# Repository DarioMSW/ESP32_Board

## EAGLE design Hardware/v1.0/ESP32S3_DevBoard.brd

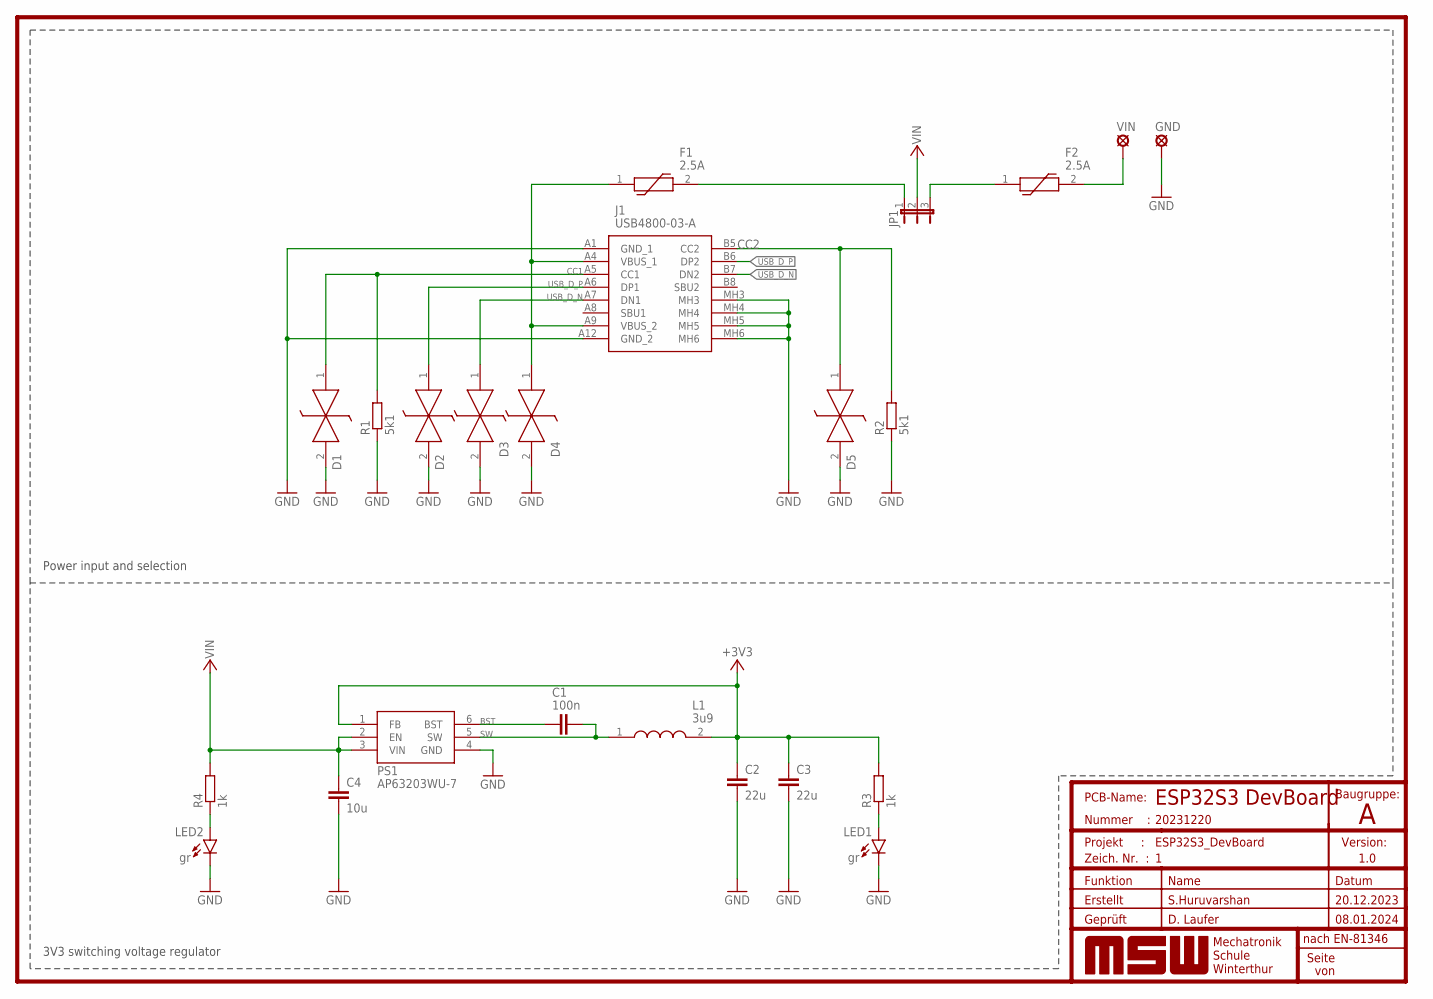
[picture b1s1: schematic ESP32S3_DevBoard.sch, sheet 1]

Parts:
C1: 100n; C0805
C2, C3: 22u; C1206
C4: 10u; C1206
D1, D2, D3, D4, D5: GG060305100N2P; DIONC1608X70N
F1, F2: 2.5A; 2920L030DR
GND: LSP10
J1: USB4800-03-A; USB480003A
JP1: JP2W
L1: 3u9; 74404052039
LED1, LED2: gr; CHIPLED_1206
PS1: AP63203WU-7; SOT95P280X100-6N
R1, R2: 5k1; R0805
R3, R4: 1k; R0805
VIN: LSP10

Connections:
+3V3: C2.1, C3.1, L1.2, PS1.1 (FB), R3.2; also elsewhere on the board
BST: C1.1, PS1.6 (BST)
CC1: D1.1 (K1), J1.A5 (CC1), R1.2
CC2: D5.1 (K1), J1.B5 (CC2), R2.2
GND: C2.2, C3.2, C4.2, D1.2 (K2), D2.2 (K2), D3.2 (K2), D4.2 (K2), D5.2 (K2), GND.MP, J1.A1 (GND_1), J1.A12 (GND_2), J1.MH3, J1.MH4, J1.MH5, J1.MH6, LED1.C, LED2.C, PS1.4 (GND), R1.1, R2.1; also elsewhere on the board
unnamed: F2.2, VIN.MP
unnamed: LED2.A, R4.1
unnamed: LED1.A, R3.1
unnamed: F1.2, JP1.1
unnamed: F2.1, JP1.3
SW: C1.2, L1.1, PS1.5 (SW)
USB_D_N: D3.1 (K1), J1.A7 (DN1), J1.B7 (DN2); also elsewhere on the board
USB_D_P: D2.1 (K1), J1.A6 (DP1), J1.B6 (DP2); also elsewhere on the board
VFUSE: D4.1 (K1), F1.1, J1.A4 (VBUS_1), J1.A9 (VBUS_2)
VTERMINAL: C4.1, JP1.2, PS1.2 (EN), PS1.3 (VIN), R4.2; also elsewhere on the board

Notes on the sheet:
Power input and selection
3V3 switching voltage regulator

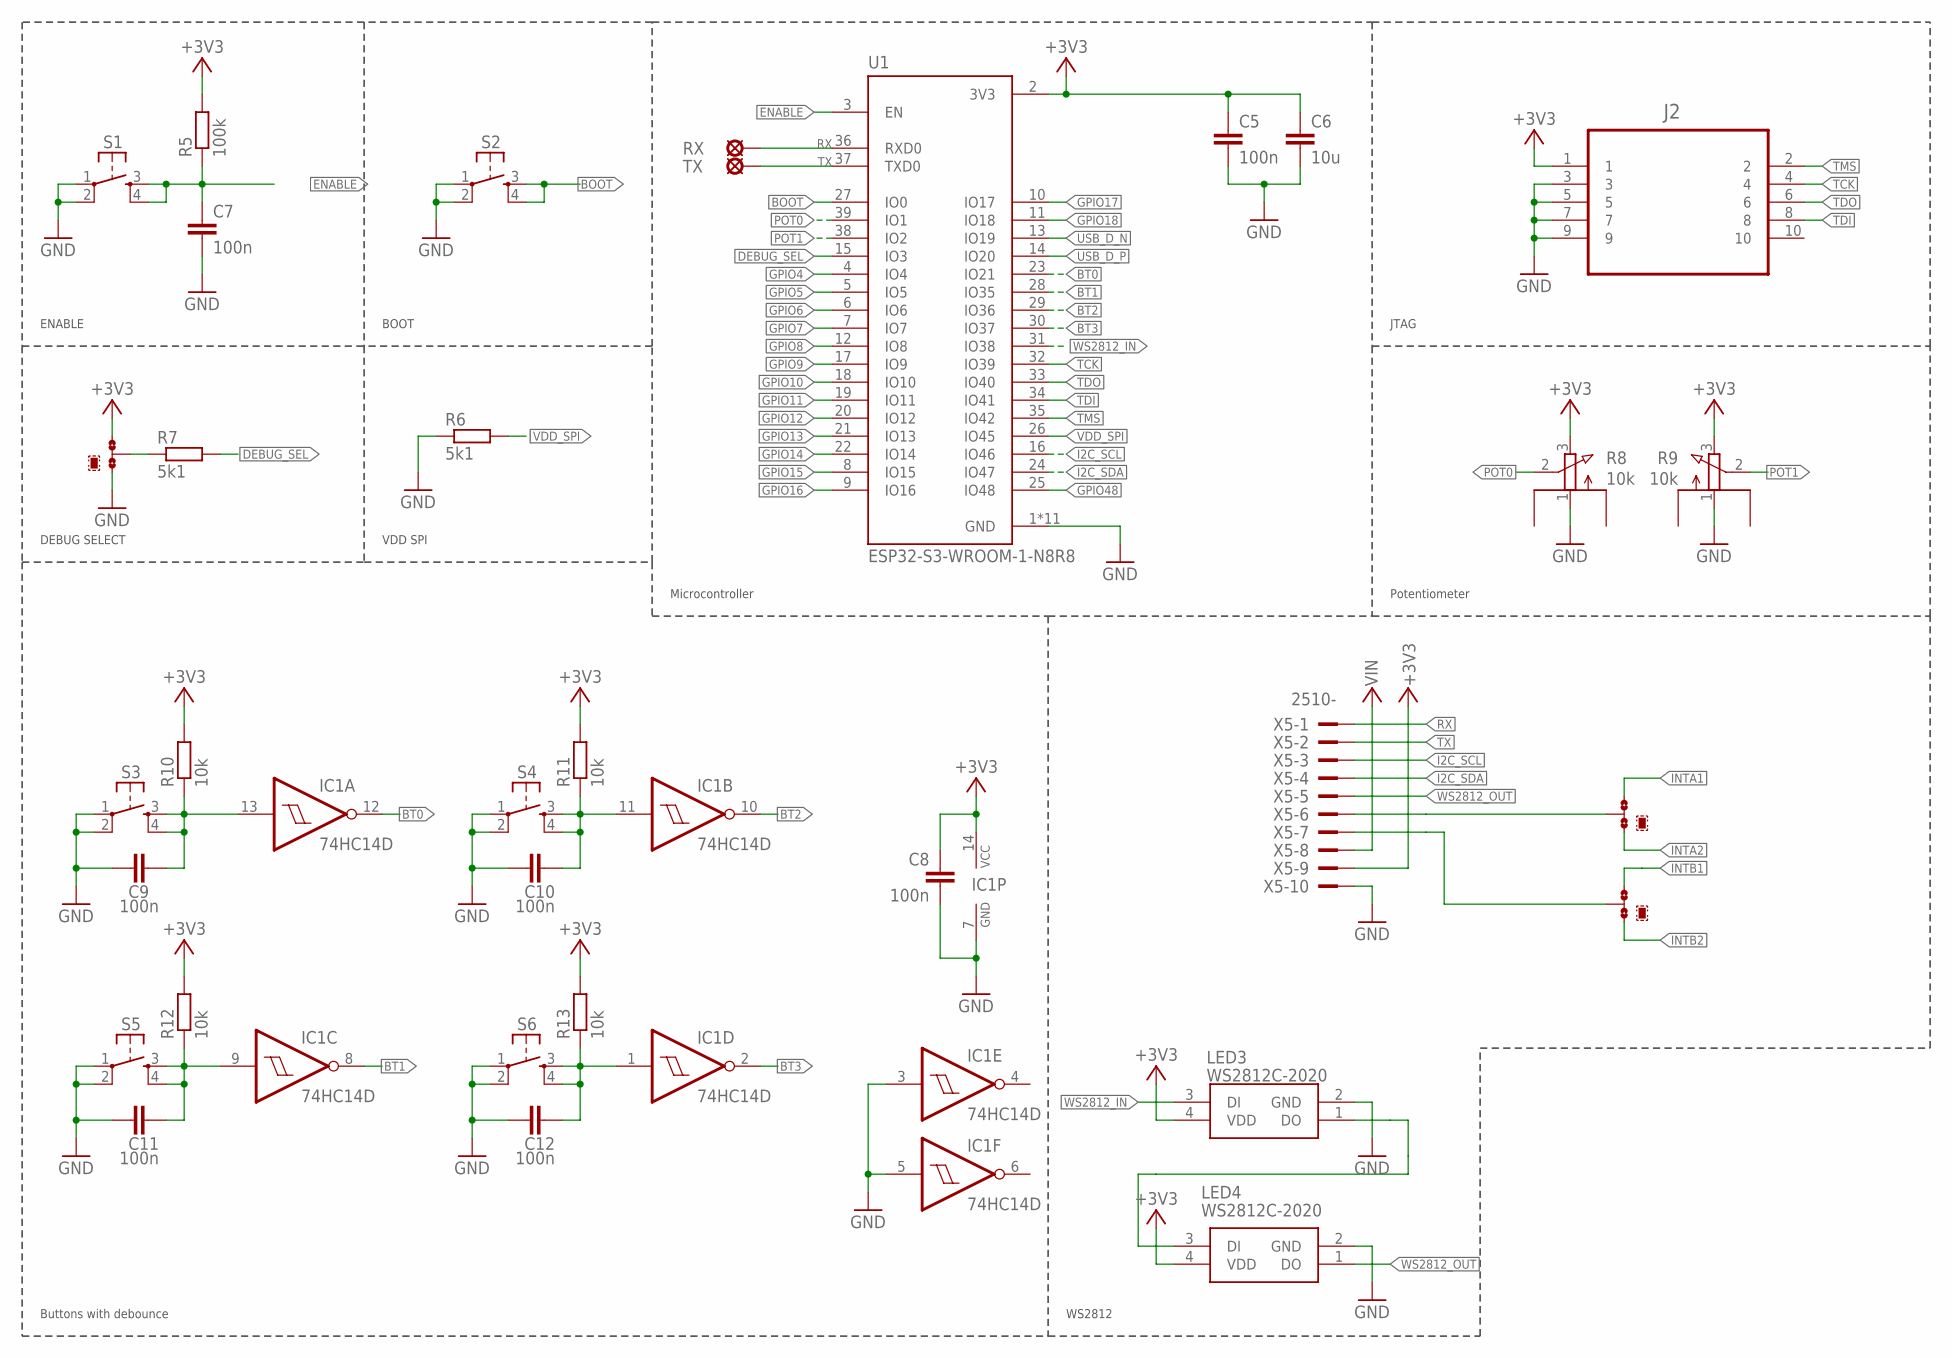
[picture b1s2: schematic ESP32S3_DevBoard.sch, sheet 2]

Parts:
C5, C7, C8, C9, C10, C11, C12: 100n; C0805
C6: 10u; C1206
IC1: 74HC14D; SO14
J2: 3220-10-0100-00; SAMTEC_FTS-105-01-L-D
JMP1, JMP2, JMP3: 0R-JUMPC; C0R-JMP
LED3, LED4: WS2812C-2020; WS2812C2020
R5: 100k; R0805
R6, R7: 5k1; R0805
R8, R9: 10k; EVUF
R10, R11, R12, R13: 10k; R0805
RX: LSP10
S1, S2, S3, S4, S5, S6: TS42_4PAD
TX: LSP10
U1: ESP32-S3-WROOM-1-N8R8; XCVR_ESP32S3WROOM1N8R8
X5: 2510-; PAK100/2500-10

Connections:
+3V3: C5.1, C6.1, C8.1, IC1.14 (VCC), J2.1, JMP1.1, LED3.4 (VDD), LED4.4 (VDD), R5.2, R8.3 (E), R9.3 (E), R10.2, R11.2, R12.2, R13.2, U1.2 (3V3), X5.9; also elsewhere on the board
BOOT: S2.3, S2.4, U1.27 (IO0)
BT0: IC1.12 (O), U1.23 (IO21)
BT1: IC1.8 (O), U1.28 (IO35)
BT2: IC1.10 (O), U1.29 (IO36)
BT3: IC1.2 (O), U1.30 (IO37)
DEBUG_SEL: R7.2, U1.15 (IO3)
ENABLE: C7.1, R5.1, S1.3, S1.4, U1.3 (EN)
GND: C5.2, C6.2, C7.2, C8.2, C9.2, C10.2, C11.2, C12.2, IC1.3 (I), IC1.5 (I), IC1.7 (GND), J2.3, J2.5, J2.7, J2.9, JMP1.3, LED3.2 (GND), LED4.2 (GND), R6.1, R8.1 (A), R9.1 (A), S1.1, S1.2, S2.1, S2.2, S3.1, S3.2, S4.1, S4.2, S5.1, S5.2, S6.1, S6.2, U1.1 (GND), U1.40 (GND), U1.41_1 (GND), U1.41_2 (GND), U1.41_3 (GND), U1.41_4 (GND), U1.41_5 (GND), U1.41_6 (GND), U1.41_7 (GND), U1.41_8 (GND), U1.41_9 (GND), X5.10; also elsewhere on the board
GPIO4: U1.4 (IO4); also elsewhere on the board
GPIO5: U1.5 (IO5); also elsewhere on the board
GPIO6: U1.6 (IO6); also elsewhere on the board
GPIO7: U1.7 (IO7); also elsewhere on the board
GPIO8: U1.12 (IO8); also elsewhere on the board
GPIO9: U1.17 (IO9); also elsewhere on the board
GPIO10: U1.18 (IO10); also elsewhere on the board
GPIO11: U1.19 (IO11); also elsewhere on the board
GPIO12: U1.20 (IO12); also elsewhere on the board
GPIO13: U1.21 (IO13); also elsewhere on the board
GPIO14: U1.22 (IO14); also elsewhere on the board
GPIO15: U1.8 (IO15); also elsewhere on the board
GPIO16: U1.9 (IO16); also elsewhere on the board
GPIO17: U1.10 (IO17); also elsewhere on the board
GPIO18: U1.11 (IO18); also elsewhere on the board
GPIO48: U1.25 (IO48); also elsewhere on the board
I2C_SCL: U1.16 (IO46), X5.3; also elsewhere on the board
I2C_SDA: U1.24 (IO47), X5.4; also elsewhere on the board
INTA1: JMP2.3; also elsewhere on the board
INTA2: JMP2.1; also elsewhere on the board
INTB1: JMP3.3; also elsewhere on the board
INTB2: JMP3.1; also elsewhere on the board
unnamed: JMP1.2, R7.1
unnamed: C9.1, IC1.13 (I), R10.1, S3.3, S3.4
unnamed: C11.1, IC1.9 (I), R12.1, S5.3, S5.4
unnamed: C10.1, IC1.11 (I), R11.1, S4.3, S4.4
unnamed: C12.1, IC1.1 (I), R13.1, S6.3, S6.4
unnamed: LED3.1 (DO), LED4.3 (DI)
unnamed: JMP2.2, X5.6
unnamed: JMP3.2, X5.7
POT0: R8.2 (S), U1.39 (IO1)
POT1: R9.2 (S), U1.38 (IO2)
RX: RX.MP, U1.36 (RXD0), X5.1
TCK: J2.4, U1.32 (IO39)
TDI: J2.8, U1.34 (IO41)
TDO: J2.6, U1.33 (IO40)
TMS: J2.2, U1.35 (IO42)
TX: TX.MP, U1.37 (TXD0), X5.2
USB_D_N: U1.13 (IO19); also elsewhere on the board
USB_D_P: U1.14 (IO20); also elsewhere on the board
VDD_SPI: R6.2, U1.26 (IO45)
VTERMINAL: X5.8; also elsewhere on the board
WS2812_IN: LED3.3 (DI), U1.31 (IO38)
WS2812_OUT: LED4.1 (DO), X5.5

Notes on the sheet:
ENABLE
DEBUG SELECT
BOOT
VDD SPI
Microcontroller
JTAG
Potentiometer
Buttons with debounce
WS2812

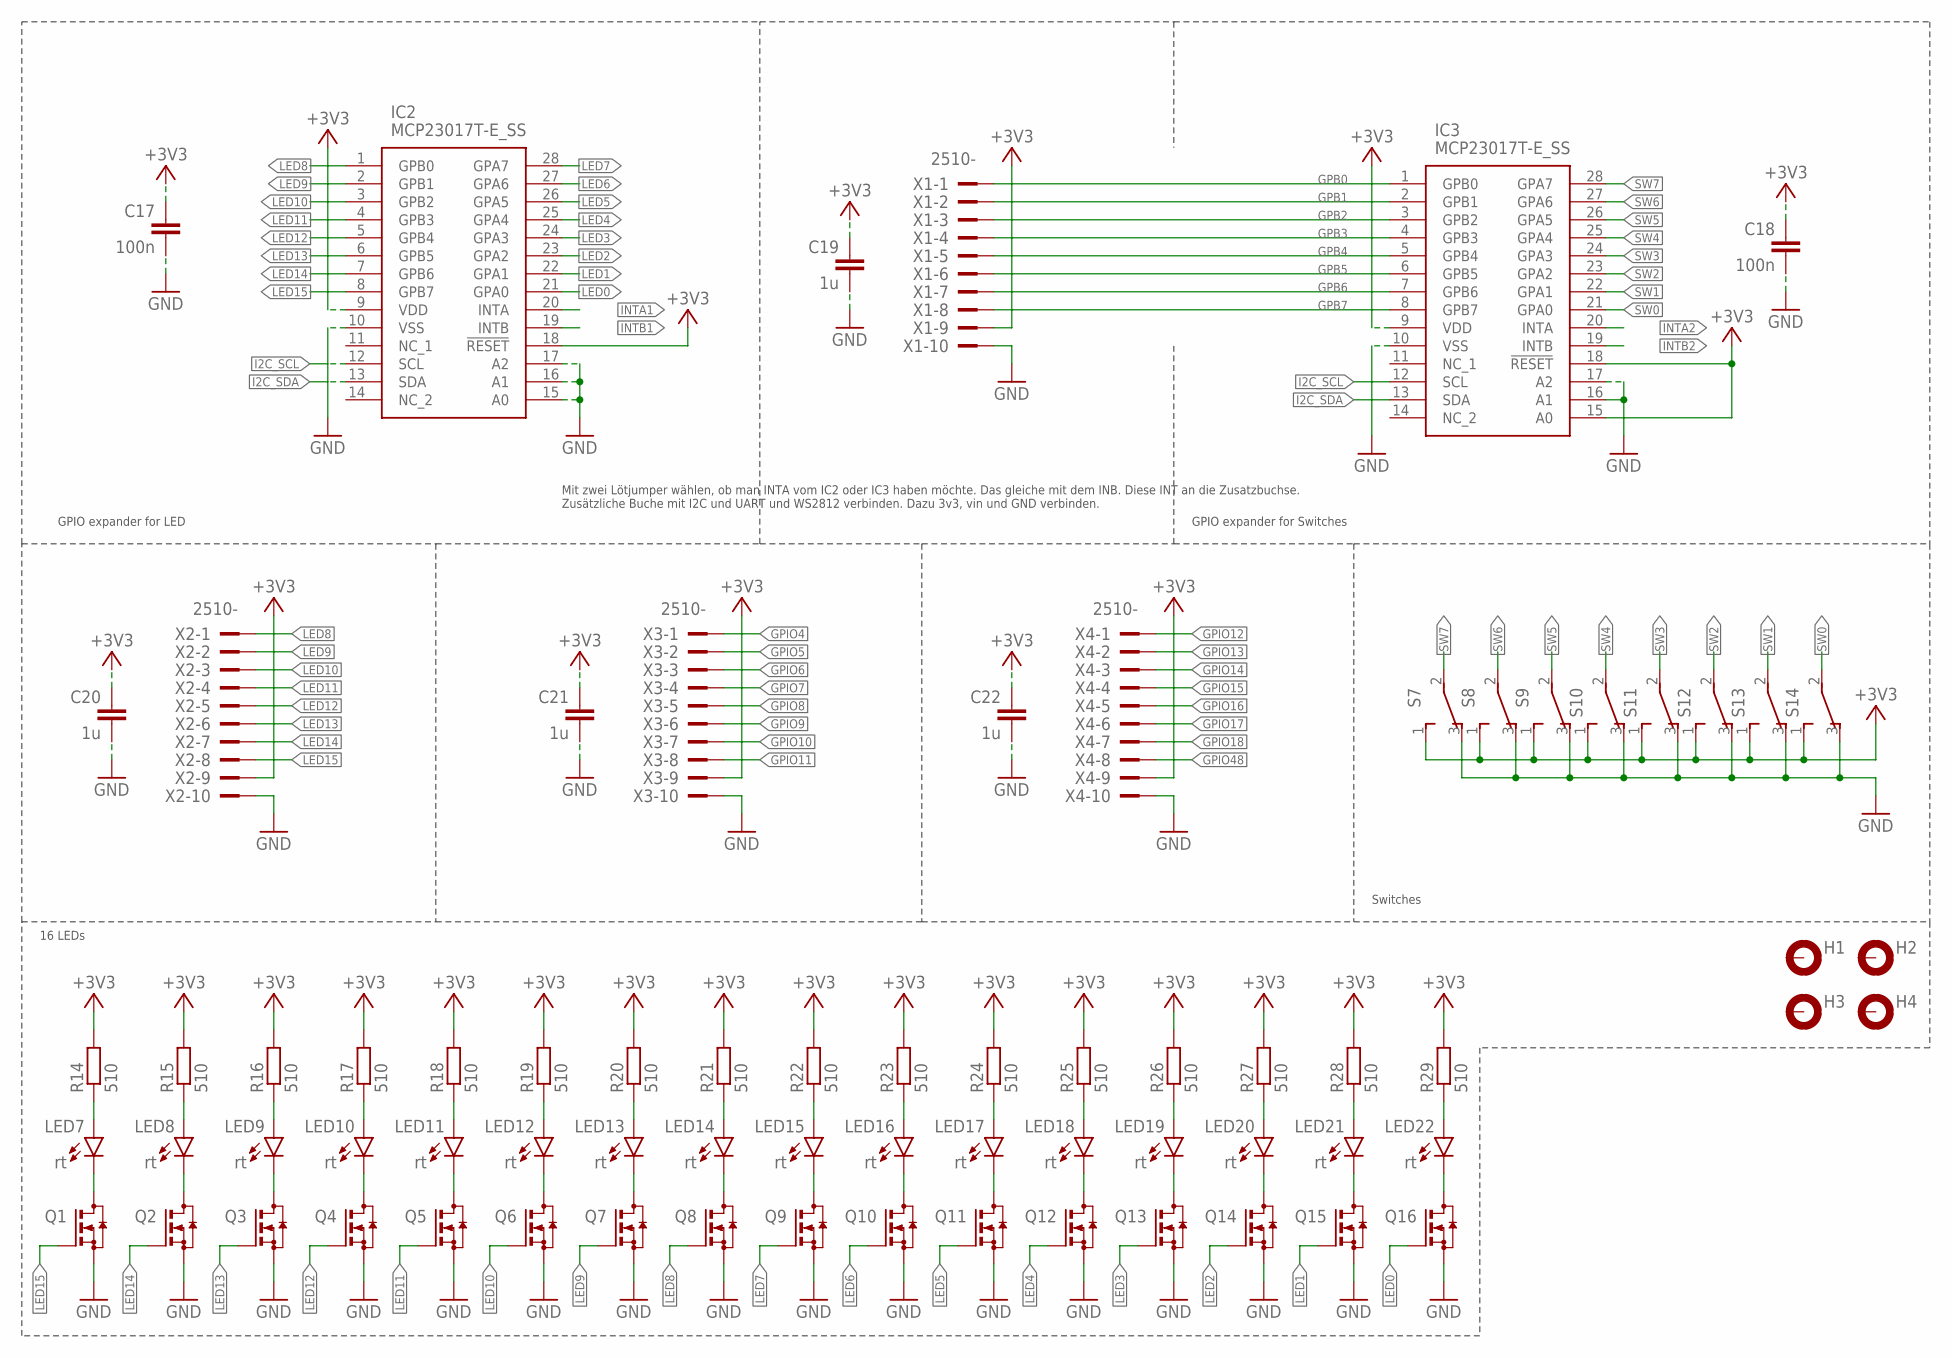
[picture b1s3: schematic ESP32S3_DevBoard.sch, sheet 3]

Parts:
C17, C18: 100n; C0805
C19, C20, C21, C22: 1u; C0805
H1, H2, H3, H4: MOUNT-PAD-ROUND3.3; 3,3-PAD
IC2, IC3: MCP23017T-E_SS; SOP65P780X200-28N
LED7, LED8, LED9, LED10, LED11, LED12, LED13, LED14, LED15, LED16, LED17, LED18, LED19, LED20, LED21, LED22: rt; CHIPLED_1206
Q1, Q2, Q3, Q4, Q5, Q6, Q7, Q8, Q9, Q10, Q11, Q12, Q13, Q14, Q15, Q16: PMV20EN; SOT23
R14, R15, R16, R17, R18, R19, R20, R21, R22, R23, R24, R25, R26, R27, R28, R29: 510; R0805
S7, S8, S9, S10, S11, S12, S13, S14: TL36POSPDT_5MM; SPDT_5MM
X1, X2, X3, X4: 2510-; PAK100/2500-10

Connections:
+3V3: C17.1, C18.1, C19.1, C20.1, C21.1, C22.1, IC2.9 (VDD), IC2.18 (!RESET), IC3.9 (VDD), IC3.15 (A0), IC3.18 (!RESET), R14.2, R15.2, R16.2, R17.2, R18.2, R19.2, R20.2, R21.2, R22.2, R23.2, R24.2, R25.2, R26.2, R27.2, R28.2, R29.2, S7.1 (S), S8.1 (S), S9.1 (S), S10.1 (S), S11.1 (S), S12.1 (S), S13.1 (S), S14.1 (S), X1.9, X2.9, X3.9, X4.9; also elsewhere on the board
GND: C17.2, C18.2, C19.2, C20.2, C21.2, C22.2, IC2.10 (VSS), IC2.15 (A0), IC2.16 (A1), IC2.17 (A2), IC3.10 (VSS), IC3.16 (A1), IC3.17 (A2), Q1.2 (S), Q2.2 (S), Q3.2 (S), Q4.2 (S), Q5.2 (S), Q6.2 (S), Q7.2 (S), Q8.2 (S), Q9.2 (S), Q10.2 (S), Q11.2 (S), Q12.2 (S), Q13.2 (S), Q14.2 (S), Q15.2 (S), Q16.2 (S), S7.3 (O), S8.3 (O), S9.3 (O), S10.3 (O), S11.3 (O), S12.3 (O), S13.3 (O), S14.3 (O), X1.10, X2.10, X3.10, X4.10; also elsewhere on the board
GPB0: IC3.1 (GPB0), X1.1
GPB1: IC3.2 (GPB1), X1.2
GPB2: IC3.3 (GPB2), X1.3
GPB3: IC3.4 (GPB3), X1.4
GPB4: IC3.5 (GPB4), X1.5
GPB5: IC3.6 (GPB5), X1.6
GPB6: IC3.7 (GPB6), X1.7
GPB7: IC3.8 (GPB7), X1.8
GPIO4: X3.1; also elsewhere on the board
GPIO5: X3.2; also elsewhere on the board
GPIO6: X3.3; also elsewhere on the board
GPIO7: X3.4; also elsewhere on the board
GPIO8: X3.5; also elsewhere on the board
GPIO9: X3.6; also elsewhere on the board
GPIO10: X3.7; also elsewhere on the board
GPIO11: X3.8; also elsewhere on the board
GPIO12: X4.1; also elsewhere on the board
GPIO13: X4.2; also elsewhere on the board
GPIO14: X4.3; also elsewhere on the board
GPIO15: X4.4; also elsewhere on the board
GPIO16: X4.5; also elsewhere on the board
GPIO17: X4.6; also elsewhere on the board
GPIO18: X4.7; also elsewhere on the board
GPIO48: X4.8; also elsewhere on the board
I2C_SCL: IC2.12 (SCL), IC3.12 (SCL); also elsewhere on the board
I2C_SDA: IC2.13 (SDA), IC3.13 (SDA); also elsewhere on the board
INTA1: IC2.20 (INTA); also elsewhere on the board
INTA2: IC3.20 (INTA); also elsewhere on the board
INTB1: IC2.19 (INTB); also elsewhere on the board
INTB2: IC3.19 (INTB); also elsewhere on the board
LED0: IC2.21 (GPA0), Q16.1 (G)
LED1: IC2.22 (GPA1), Q15.1 (G)
LED2: IC2.23 (GPA2), Q14.1 (G)
LED3: IC2.24 (GPA3), Q13.1 (G)
LED4: IC2.25 (GPA4), Q12.1 (G)
LED5: IC2.26 (GPA5), Q11.1 (G)
LED6: IC2.27 (GPA6), Q10.1 (G)
LED7: IC2.28 (GPA7), Q9.1 (G)
LED8: IC2.1 (GPB0), Q8.1 (G), X2.1
LED9: IC2.2 (GPB1), Q7.1 (G), X2.2
LED10: IC2.3 (GPB2), Q6.1 (G), X2.3
LED11: IC2.4 (GPB3), Q5.1 (G), X2.4
LED12: IC2.5 (GPB4), Q4.1 (G), X2.5
LED13: IC2.6 (GPB5), Q3.1 (G), X2.6
LED14: IC2.7 (GPB6), Q2.1 (G), X2.7
LED15: IC2.8 (GPB7), Q1.1 (G), X2.8
unnamed: LED14.C, Q8.3 (D)
unnamed: LED14.A, R21.1
unnamed: LED15.C, Q9.3 (D)
unnamed: LED15.A, R22.1
unnamed: LED16.C, Q10.3 (D)
unnamed: LED16.A, R23.1
unnamed: LED17.C, Q11.3 (D)
unnamed: LED17.A, R24.1
unnamed: LED18.C, Q12.3 (D)
unnamed: LED18.A, R25.1
unnamed: LED19.C, Q13.3 (D)
unnamed: LED19.A, R26.1
unnamed: LED20.C, Q14.3 (D)
unnamed: LED20.A, R27.1
unnamed: LED21.C, Q15.3 (D)
unnamed: LED21.A, R28.1
unnamed: LED22.C, Q16.3 (D)
unnamed: LED22.A, R29.1
unnamed: LED13.C, Q7.3 (D)
unnamed: LED13.A, R20.1
unnamed: LED12.C, Q6.3 (D)
unnamed: LED12.A, R19.1
unnamed: LED11.C, Q5.3 (D)
unnamed: LED11.A, R18.1
unnamed: LED10.C, Q4.3 (D)
unnamed: LED10.A, R17.1
unnamed: LED9.C, Q3.3 (D)
unnamed: LED9.A, R16.1
unnamed: LED8.C, Q2.3 (D)
unnamed: LED8.A, R15.1
unnamed: LED7.C, Q1.3 (D)
unnamed: LED7.A, R14.1
SW0: IC3.21 (GPA0), S14.2
SW1: IC3.22 (GPA1), S13.2
SW2: IC3.23 (GPA2), S12.2
SW3: IC3.24 (GPA3), S11.2
SW4: IC3.25 (GPA4), S10.2
SW5: IC3.26 (GPA5), S9.2
SW6: IC3.27 (GPA6), S8.2
SW7: IC3.28 (GPA7), S7.2

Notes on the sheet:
GPIO expander for LED
GPIO expander for Switches
Switches
16 LEDs
Mit zwei Lötjumper wählen, ob man INTA vom IC2 oder IC3 haben möchte. Das gleiche mit dem INB. Diese INT an die Zusatzbuchse. Zusätzliche Buche mit I2C und UART und WS2812 verbinden. Dazu 3v3, vin und GND verbinden.

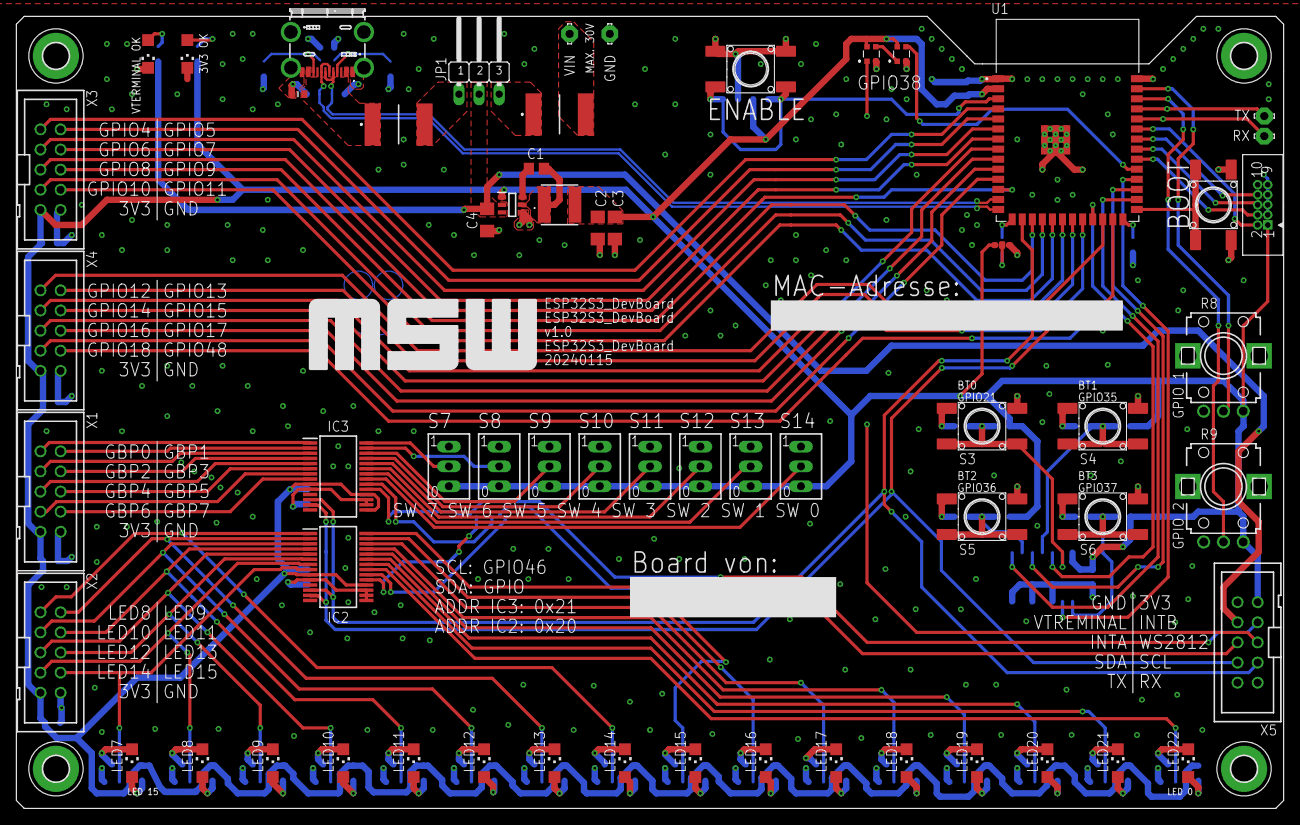
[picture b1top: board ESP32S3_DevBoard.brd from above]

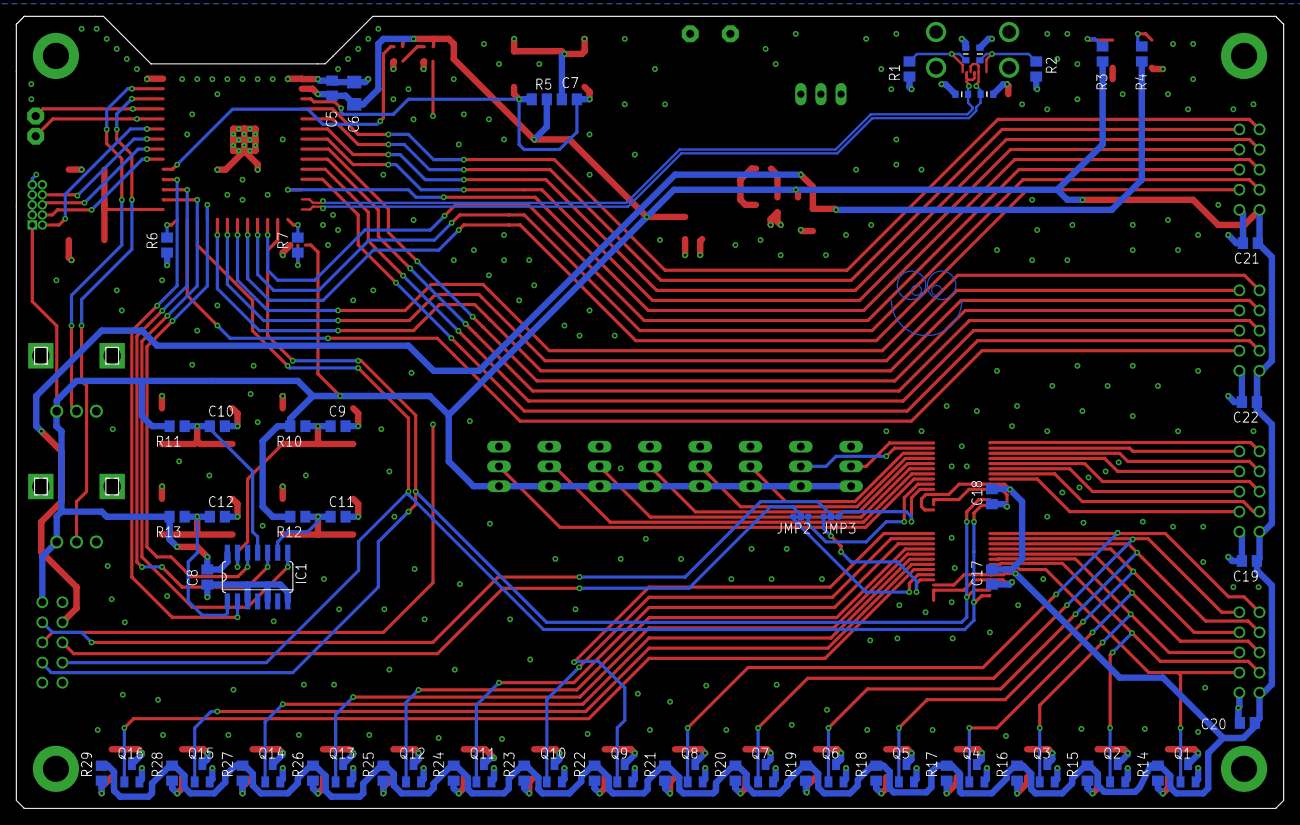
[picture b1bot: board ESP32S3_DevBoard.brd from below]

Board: 4 copper layers, 160.0 x 100.0 mm, 131 parts (64 on the bottom side), 127 nets.

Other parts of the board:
U$1: PCB_BESCHRIFTUNG
U$5: PCB_LOGO_3_28MM5

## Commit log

2025-01-31 Before New Driver
2025-01-31 New I2C-Driver
    Made with DeepSeek AI
2025-02-07 Schematic, Layout and Gerber added
2026-02-05 add gitignore
2026-02-05 moved gitignore
2026-02-05 git ignore
2026-02-05 removed build folder
2026-02-05 update ignore
2026-02-05 removed .vscode
2026-02-05 sdkconfig in gitignore
2026-02-05 sdkconfig removed
2026-02-05 Absoluter pfad entfernt
2026-02-05 Funktionierendes Beispiel ESP-Board
2026-02-05 Solve new i2c driver error
    Using the nue i2c driver we have to reset SDA and SCL Pin after boot.
